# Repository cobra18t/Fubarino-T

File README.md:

fubarino: Social Hardware and Software
========
Main Project Pages are:
http://fubarino.org

The Fubarino SD board brings affordable, breadboard compatible high speed computing power to the Arduino-compatible chipKIT/MPIDE platform. It is able to run almost all Arduino sketches right out of the box at a great price, and includes more memory, speed, and I/O pins than a typical Arduino or clone. And it includes a microSD card slot for easy sketch access to huge file storage.

cobra18t's FubarinoSDt (still in beta testing, files will be added soon)
======
This is an edited version of Brian Schmalz's original FubarinoSD. The main changes are as follows:
* Used the PIC32MX440F512, which has 512k flash memory, versus the normal 256k.
* Used a different SD socket and brought the Card Detect out to a change notification pin (A14)
* Used a 800mA regulator for just a little more *umph*
* Used Sparkfun's locking headers so breadboarding does not necessarily require soldering
* Minor layout changes to adhere to my board fabricators design rules
* Changed packages for crystal and diodes for cost reasons
* Blue LED on pin 21...you gotta love the blue!

FubarinoSD
======
Class on a stick. Course materials can fit on the SD card. The device mounts as a USB device. Unfortunatley, at 1.0 speeds. But 
it wll cut 45 minutes of getting started to 15 minutes. When offering online course using electronics, all the course materials can be placed on the board.

The goal with the project is two have two boards that are excellent for small, and bread boardable projects.

Social Hardware:
=====
* Open Source
* Open Hardware
* Sharable

Licensing
====
The Fubarino SD hardware is licenced under the Solderpad Hardware License v0.5. All MPIDE source code is licenced under GPL or other open source software licenses.

Availability:
========
These boards are Open Hardware and all the files are management in this project, and are licensed as OpenSource.
They can be created from the Eagle files right away or purchased at [Seeed Studio](http://www.seeedstudio.com/depot/fubarino-sd-p-1265.html?cPath=132_133).

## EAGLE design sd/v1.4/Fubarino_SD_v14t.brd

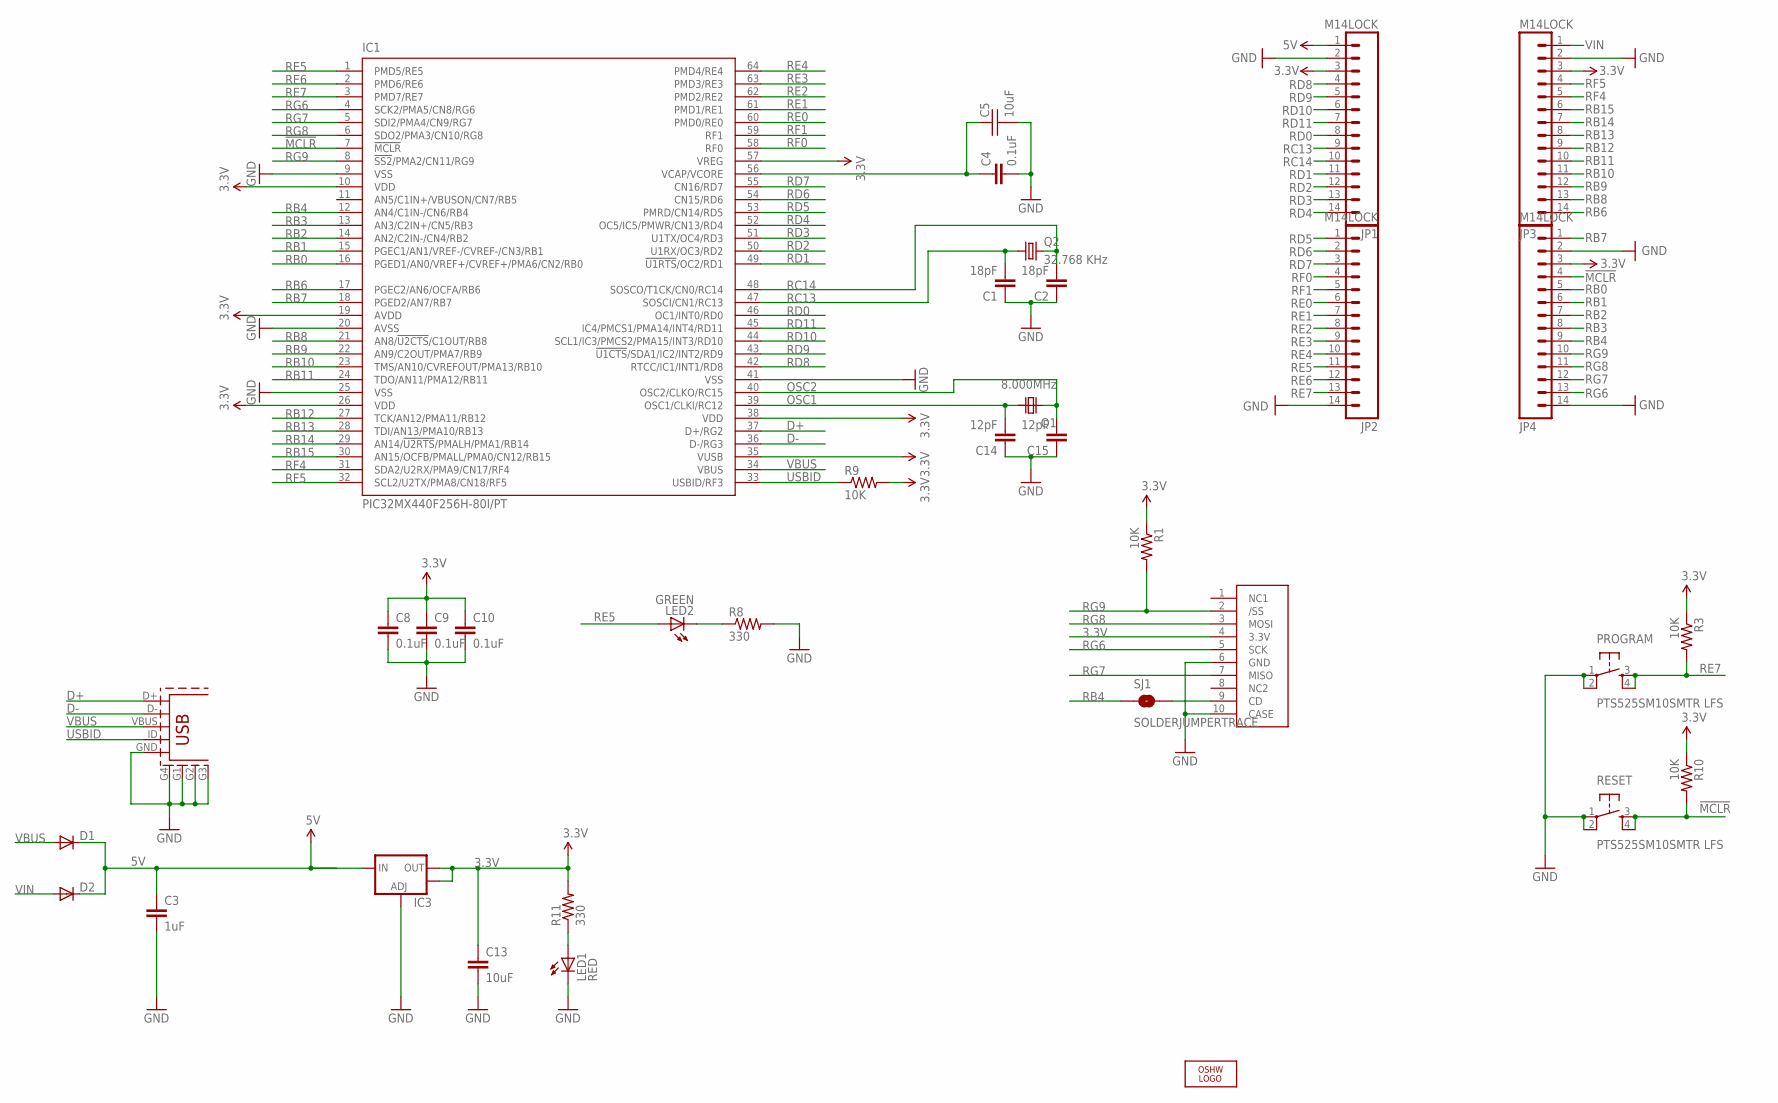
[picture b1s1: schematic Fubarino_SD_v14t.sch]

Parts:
C1, C2: 18pF; 0603-CAP
C3: 1uF; 0603-CAP
C4, C8, C9: 0.1uF; 0603-CAP
C5: 10uF; CAP_0805
C10: 0.1uF; 0603
C13: 10uF; 0805
C14, C15: 12pF; 0603-CAP
D1, D2: DIODE-SOD123; SOD123
IC1: PIC32MX440F256H-80I/PT; TQFP64-10X10
IC3: V_REG_LM1117SOT223; SOT223
J8: UX60A-MB-5ST; USB-MINIB
JP1, JP2, JP3, JP4: M14LOCK; 1X14_LOCK
LED1: RED; LED-0603
LED2: GREEN; LED-0603
LOGO1: OSHW_LOGO_8MILX0070-NT; OSHW_8X70_NOTEXT
PROGRAM: PTS525SM10SMTR LFS; TACTILE_SWITCH_SMD
Q1: 8.000MHz; 6035_METRIC
Q2: 32.768 KHz; TC26H
R1, R3, R9, R10: 10K; 0603-RES
R8, R11: 330; 0603-RES
RESET: PTS525SM10SMTR LFS; TACTILE_SWITCH_SMD
SJ1: SOLDERJUMPERTRACE; SJ_2S-TRACE
U$2: SDCARDMICROSD1; MICROSD

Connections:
3.3V: C8.1, C9.1, C10.1, C13.1, IC1.10 (VDD), IC1.19 (AVDD), IC1.26 (VDD), IC1.35 (VUSB), IC1.38 (VDD), IC1.57 (VREG), IC3.2 (OUT), IC3.4 (OUT), JP1.3, JP3.3, JP4.3, R1.1, R3.1, R9.2, R10.1, R11.2, U$2.4 (3.3V)
5V: C3.1, D1.C, D2.C, IC3.3 (IN), JP1.1
!MCLR!: IC1.7 (!MCLR), JP4.4, R10.2, RESET.3, RESET.4
D+: IC1.37 (D+/RG2), J8.D+
D-: IC1.36 (D-/RG3), J8.D-
GND: C1.1, C2.1, C3.2, C4.2, C5.2, C8.2, C9.2, C10.2, C13.2, C14.1, C15.1, IC1.9 (VSS), IC1.20 (AVSS), IC1.25 (VSS), IC1.41 (VSS), IC3.1 (ADJ), J8.G1, J8.G2, J8.G3, J8.G4 (SHIELD), J8.GND, JP1.2, JP2.14, JP3.2, JP4.2, JP4.14, LED1.C, PROGRAM.1, PROGRAM.2, R8.2, RESET.1, RESET.2, U$2.6 (GND), U$2.10 (CASE)
unnamed: SJ1.2, U$2.9 (CD)
unnamed: LED1.A, R11.1
unnamed: LED2.C, R8.1
unnamed: C4.1, C5.1, IC1.56 (VCAP/VCORE)
OSC1: C14.2, IC1.39 (OSC1/CLKI/RC12), Q1.P$1
OSC2: C15.2, IC1.40 (OSC2/CLKO/RC15), Q1.P$2
RB0: IC1.16 (PGED1/AN0/VREF+/CVREF+/PMA6/CN2/RB0), JP4.5
RB1: IC1.15 (PGEC1/AN1/VREF-/CVREF-/CN3/RB1), JP4.6
RB2: IC1.14 (AN2/C2IN-/CN4/RB2), JP4.7
RB3: IC1.13 (AN3/C2IN+/CN5/RB3), JP4.8
RB4: IC1.12 (AN4/C1IN-/CN6/RB4), JP4.9, SJ1.1
RB6: IC1.17 (PGEC2/AN6/OCFA/RB6), JP3.14
RB7: IC1.18 (PGED2/AN7/RB7), JP4.1
RB8: IC1.21 (AN8/!U2CTS!/C1OUT/RB8), JP3.13
RB9: IC1.22 (AN9/C2OUT/PMA7/RB9), JP3.12
RB10: IC1.23 (TMS/AN10/CVREFOUT/PMA13/RB10), JP3.11
RB11: IC1.24 (TDO/AN11/PMA12/RB11), JP3.10
RB12: IC1.27 (TCK/AN12/PMA11/RB12), JP3.9
RB13: IC1.28 (TDI/AN13/PMA10/RB13), JP3.8
RB14: IC1.29 (AN14/!U2RTS!/PMALH/PMA1/RB14), JP3.7
RB15: IC1.30 (AN15/OCFB/PMALL/PMA0/CN12/RB15), JP3.6
RC13: C1.2, IC1.47 (SOSCI/CN1/RC13), JP1.9, Q2.1
RC14: C2.2, IC1.48 (SOSCO/T1CK/CN0/RC14), JP1.10, Q2.2
RD0: IC1.46 (OC1/INT0/RD0), JP1.8
RD1: IC1.49 (!U1RTS!/OC2/RD1), JP1.11
RD2: IC1.50 (U1RX/OC3/RD2), JP1.12
RD3: IC1.51 (U1TX/OC4/RD3), JP1.13
RD4: IC1.52 (OC5/IC5/PMWR/CN13/RD4), JP1.14
RD5: IC1.53 (PMRD/CN14/RD5), JP2.1
RD6: IC1.54 (CN15/RD6), JP2.2
RD7: IC1.55 (CN16/RD7), JP2.3
RD8: IC1.42 (RTCC/IC1/INT1/RD8), JP1.4
RD9: IC1.43 (!U1CTS!/SDA1/IC2/INT2/RD9), JP1.5
RD10: IC1.44 (SCL1/IC3/PMCS2/PMA15/INT3/RD10), JP1.6
RD11: IC1.45 (IC4/PMCS1/PMA14/INT4/RD11), JP1.7
RE0: IC1.60 (PMD0/RE0), JP2.6
RE1: IC1.61 (PMD1/RE1), JP2.7
RE2: IC1.62 (PMD2/RE2), JP2.8
RE3: IC1.63 (PMD3/RE3), JP2.9
RE4: IC1.64 (PMD4/RE4), JP2.10
RE5: IC1.1 (PMD5/RE5), JP2.11, LED2.A
RE6: IC1.2 (PMD6/RE6), JP2.12
RE7: IC1.3 (PMD7/RE7), JP2.13, PROGRAM.3, PROGRAM.4, R3.2
RF0: IC1.58 (RF0), JP2.4
RF1: IC1.59 (RF1), JP2.5
RF4: IC1.31 (SDA2/U2RX/PMA9/CN17/RF4), JP3.5
RF5: IC1.32 (SCL2/U2TX/PMA8/CN18/RF5), JP3.4
RG6: IC1.4 (SCK2/PMA5/CN8/RG6), JP4.13, U$2.5 (SCK)
RG7: IC1.5 (SDI2/PMA4/CN9/RG7), JP4.12, U$2.7 (MISO)
RG8: IC1.6 (SDO2/PMA3/CN10/RG8), JP4.11, U$2.3 (MOSI)
RG9: IC1.8 (!SS2!/PMA2/CN11/RG9), JP4.10, R1.2, U$2.2 (/SS)
USBID: IC1.33 (USBID/RF3), J8.ID (USB_ID), R9.1
VBUS: D1.A, IC1.34 (VBUS), J8.VBUS
VIN: D2.A, JP3.1

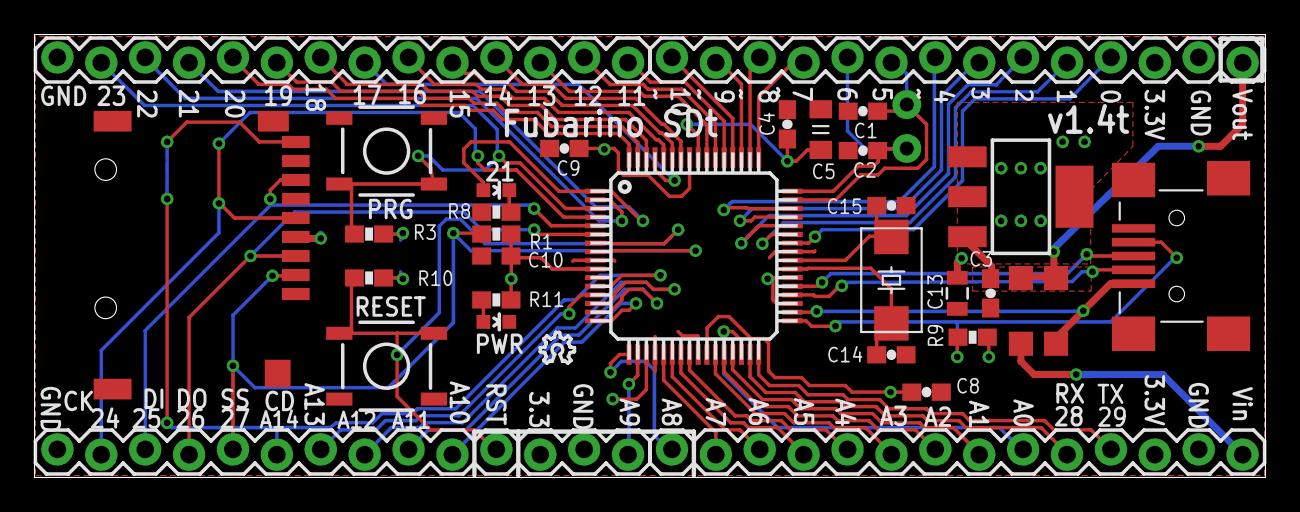
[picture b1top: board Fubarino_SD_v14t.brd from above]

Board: 2 copper layers, 71.2 x 25.6 mm, 35 parts (1 on the bottom side), 60 nets.

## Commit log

2012-12-20 Upload preliminary Eagle 6.3 files for FubarinoSDt Signed-off-by: cobra18t <>
2013-01-14 Adjusted pads/holes for SD, buttons, and lock headers: cobra18t <https://github.com/cobra18t>
2013-01-14 Added bootloader and layout image
2013-01-14 Move image to "sd" folder

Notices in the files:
sd/v1.4/Fubarino_SD_v14t.brd:
Copyright 2012 Brian Schmalz Copyright and related rights are licensed under the Solderpad Hardware License, Version 0.51 (the “License”);
software, hardware and materials distributed under this License is distributed on an “AS IS” BASIS, WITHOUT WARRANTIES OR CONDITIONS OF ANY KIND, either express or implied.
Edited by Thomas Fulenwider, 11/02/2012. Released under the same Solderpad Hardware License.
